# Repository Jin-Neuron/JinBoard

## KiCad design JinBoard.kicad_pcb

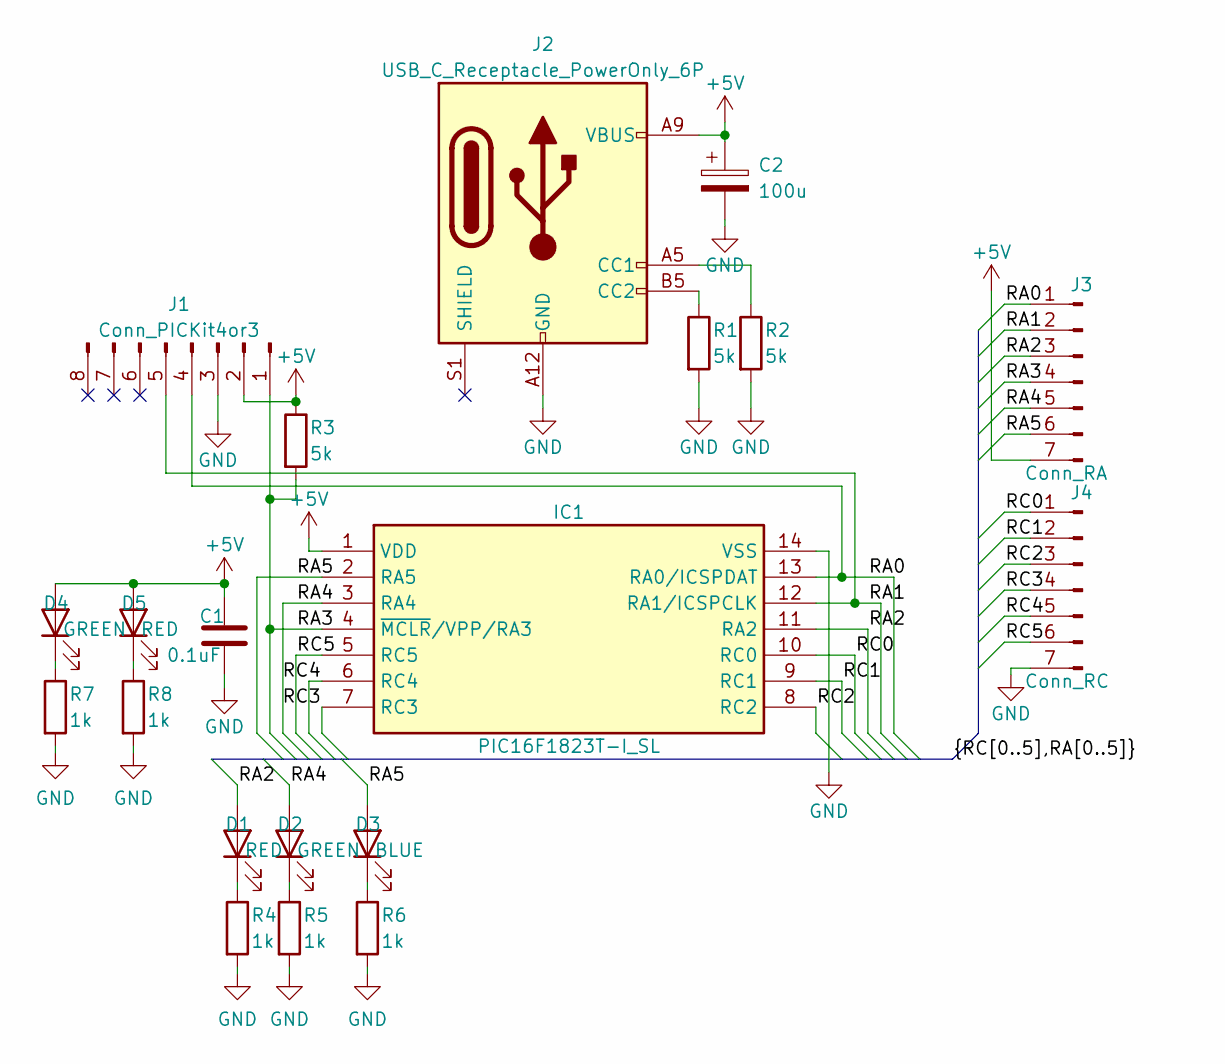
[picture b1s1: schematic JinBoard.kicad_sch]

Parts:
C1: 0.1uF; C_0603_1608Metric
C2: 100u; CP_Radial_D6.3mm_P2.50mm
D1, D5: RED; LED_0603_1608Metric
D2, D4: GREEN; LED_0603_1608Metric
D3: BLUE; LED_0603_1608Metric
IC1: PIC16F1823T-I_SL; SOIC127P600X175-14N; Mouser Part Number 579-PIC16F1823T-I/SL
J1: Conn_PICKit4or3; PinHeader_1x08_P2.54mm_Horizontal
J2: USB_C_Receptacle_PowerOnly_6P; USB_C_Receptacle_GCT_USB4135-GF-A_6P_TopMnt_Horizontal
J3: Conn_RA; PinHeader_1x07_P2.54mm_Vertical
J4: Conn_RC; PinHeader_1x07_P2.54mm_Vertical
R1, R2, R3: 5k; R_0603_1608Metric
R4, R5, R6, R7, R8: 1k; R_0603_1608Metric

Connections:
+5V: C1.1, C2.1, D4.2 (A), D5.2 (A), IC1.1 (VDD), J1.2, J2.A9 (VBUS), J2.B9 (VBUS), J3.7, R3.1
/RA0: IC1.13 (RA0/ICSPDAT), J1.4, J3.1
/RA1: IC1.12 (RA1/ICSPCLK), J1.5, J3.2
/RA2: D1.2 (A), IC1.11 (RA2), J3.3
/RA3: IC1.4 (~MCLR/VPP/RA3), J1.1, J3.4, R3.2
/RA4: D2.2 (A), IC1.3 (RA4), J3.5
/RA5: D3.2 (A), IC1.2 (RA5), J3.6
/RC0: IC1.10 (RC0), J4.1
/RC1: IC1.9 (RC1), J4.2
/RC2: IC1.8 (RC2), J4.3
/RC3: IC1.7 (RC3), J4.4
/RC4: IC1.6 (RC4), J4.5
/RC5: IC1.5 (RC5), J4.6
GND: C1.2, C2.2, IC1.14 (VSS), J1.3, J2.A12 (GND), J2.B12 (GND), J4.7, R1.2, R2.2, R4.2, R5.2, R6.2, R7.2, R8.2
unnamed: D1.1 (K), R4.1
unnamed: D2.1 (K), R5.1
unnamed: D3.1 (K), R6.1
unnamed: D4.1 (K), R7.1
unnamed: D5.1 (K), R8.1
unnamed: J2.A5 (CC1), R2.1
unnamed: J2.B5 (CC2), R1.1

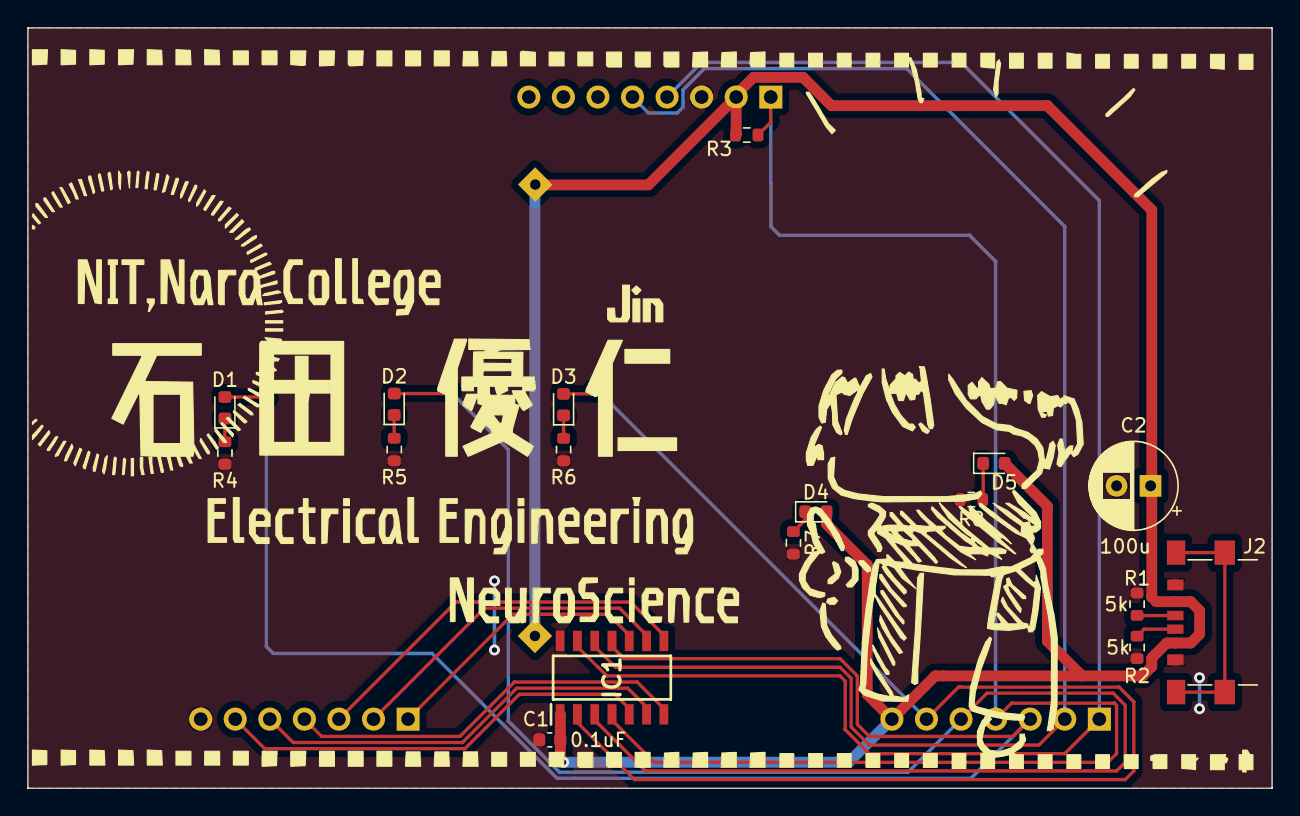
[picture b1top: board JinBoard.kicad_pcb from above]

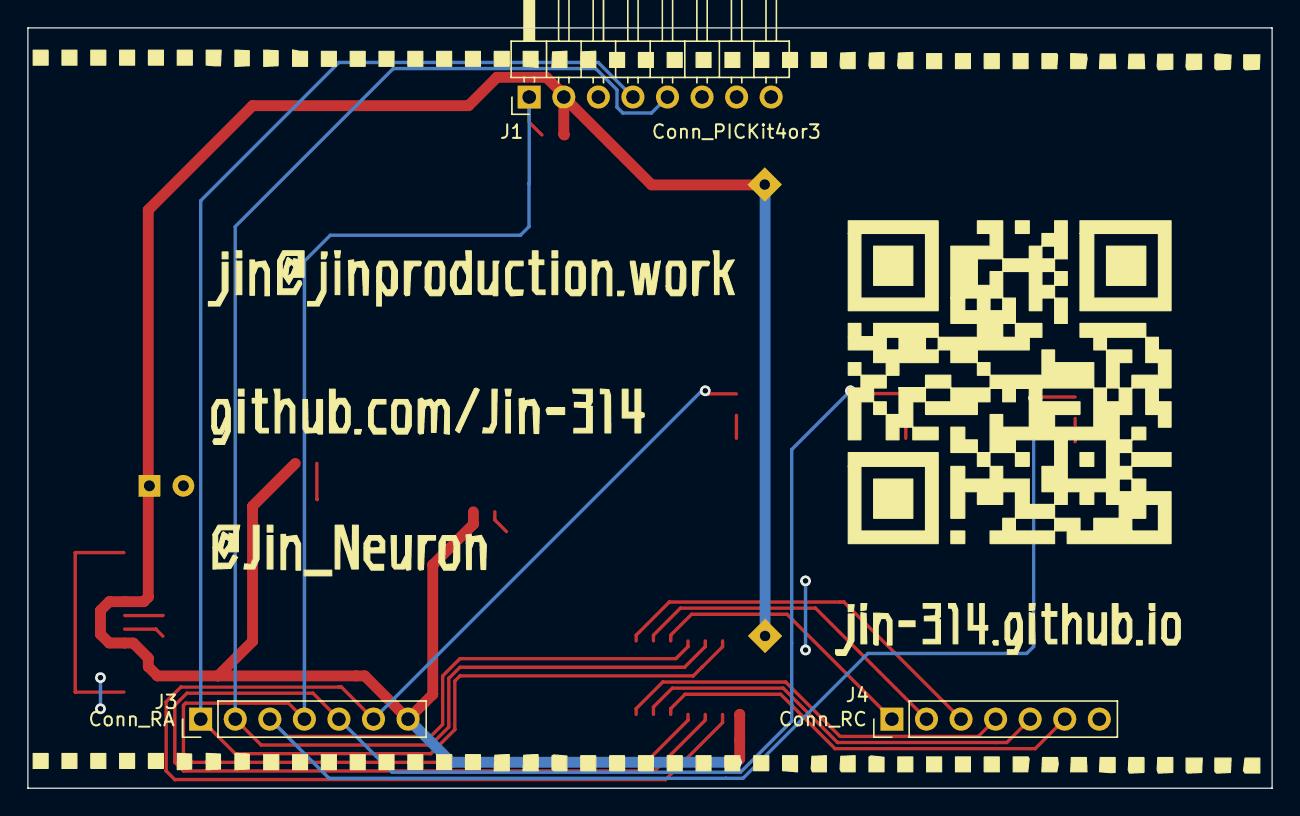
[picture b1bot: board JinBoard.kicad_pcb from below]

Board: 2 copper layers, 91.4 x 55.9 mm, 20 parts (3 on the bottom side), 21 nets.

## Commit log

2023-05-26 add gitignore
2023-05-26 gitignore apply
2023-05-26 add pic
2023-06-13 add Source
2023-06-13 ignore
